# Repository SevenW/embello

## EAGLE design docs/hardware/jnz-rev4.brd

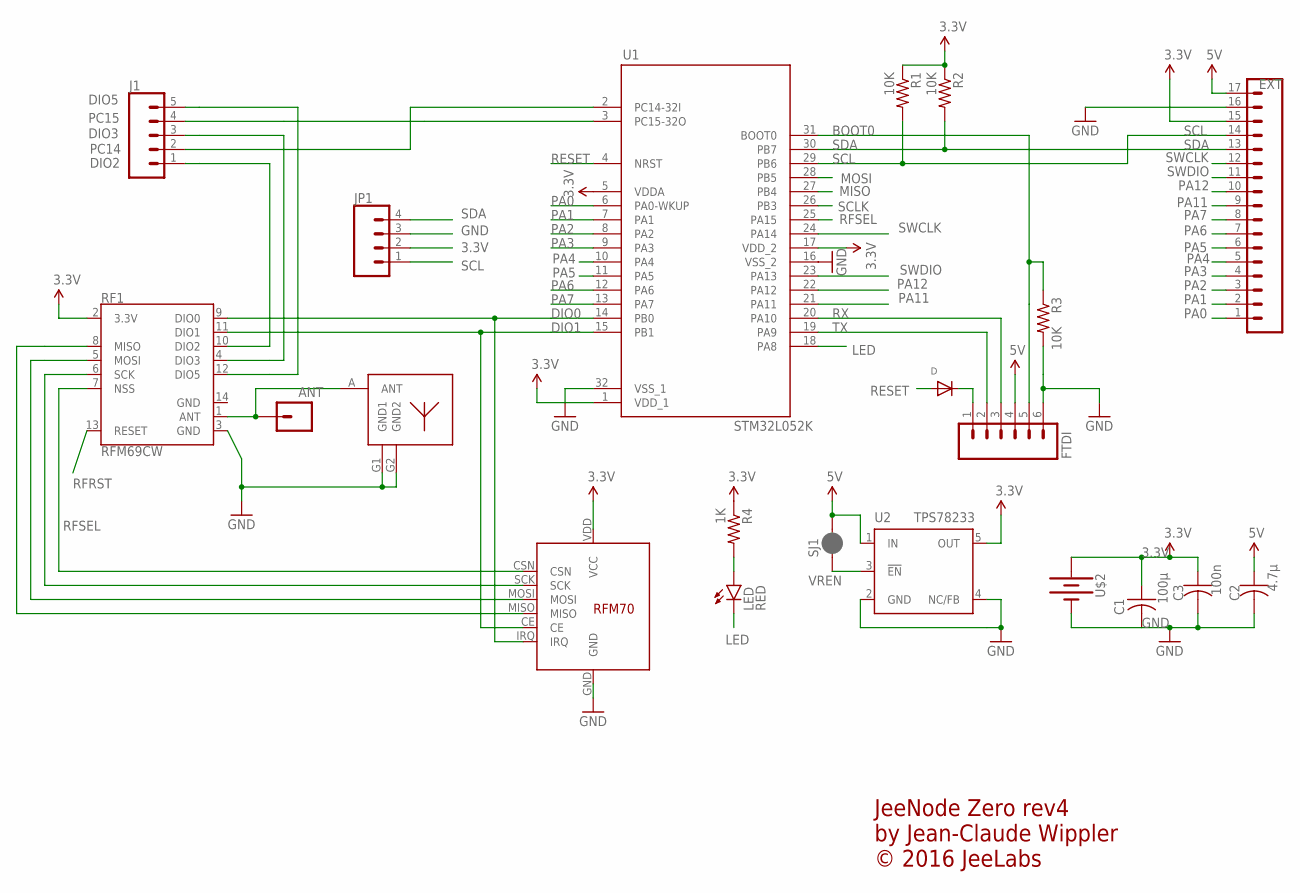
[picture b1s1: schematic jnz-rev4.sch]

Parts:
ANT: CONN_01PTH_NO_SILK_KIT; 1X01NS_KIT
C1: 100µ; C1206
C2: 4.7µ; C0805
C3: 100n; C0603
D: DIODESOD-323F; SOD-323F
EXT: CONN_17NOSILK; 1X17_NO_SILK
FTDI: CONN_06NO_SILK_FEMALE_PTH; 1X06_NO_SILK
J1: CONN_05NO_SILK; 1X05_NO_SILK
JP1: CONN_04SMD_RA_FEMALE; 1X04_SMD_RA_FEMALE
LED: RED; LED-0603
R1, R2, R3: 10K; R0603
R4: 1K; R0603
RF1: RFM69CW; RFM69CW-XXXS2
RF2: RFM75; RFM70
SJ1: JUMPER-SMT_2_NC_PASTE_NO-SILK; SMT-JUMPER_2_NC_PASTE_NO-SILK
U1: STM32L052K; TQFP32-08
U2: TPS78233; SOT23-DBV
U$1: UFL
U$2: BATTERY-20MM_SMD_4LEGS; BATTCON_20MM_4LEGS

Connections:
3.3V: C1.1, C3.1, EXT.15, JP1.2, R1.1, R2.1, R4.1, RF1.2 (3.3V), RF2.VDD (VCC), U1.1 (VDD_1), U1.5 (VDDA), U1.17 (VDD_2), U2.5 (OUT), U$2.POSITIVE@1 (+), U$2.POSITIVE@2 (+), U$2.POSITIVE@3 (+), U$2.POSITIVE@4 (+)
5V: C2.1, EXT.17, FTDI.4, SJ1.2, U2.1 (IN)
BOOT0: FTDI.5, R3.1, U1.31 (BOOT0)
DIO0: RF1.9 (DIO0), RF2.IRQ, U1.14 (PB0)
DIO1: RF1.11 (DIO1), RF2.CE, U1.15 (PB1)
DIO2: J1.1, RF1.10 (DIO2)
DIO3: J1.3, RF1.4 (DIO3)
DIO5: J1.5, RF1.12 (DIO5)
GND: C1.2, C2.2, C3.2, EXT.16, FTDI.6, JP1.3, R3.2, RF1.3 (GND), RF1.14 (GND), RF2.GND, U1.16 (VSS_2), U1.32 (VSS_1), U2.2 (GND), U2.4 (NC/FB), U$1.G1 (GND1), U$1.G2 (GND2), U$2.NEGATIVE (-)
LED: LED.C, U1.18 (PA8)
MISO: RF1.8 (MISO), RF2.MISO, U1.27 (PB4)
MOSI: RF1.5 (MOSI), RF2.MOSI, U1.28 (PB5)
unnamed: D.C, FTDI.1
unnamed: LED.A, R4.2
unnamed: ANT.1, RF1.1 (ANT), U$1.A (ANT)
PA0: EXT.1, U1.6 (PA0-WKUP)
PA1: EXT.2, U1.7 (PA1)
PA2: EXT.3, U1.8 (PA2)
PA3: EXT.4, U1.9 (PA3)
PA4: EXT.5, U1.10 (PA4)
PA5: EXT.6, U1.11 (PA5)
PA6: EXT.7, U1.12 (PA6)
PA7: EXT.8, U1.13 (PA7)
PA11: EXT.9, U1.21 (PA11)
PA12: EXT.10, U1.22 (PA12)
PC14: J1.2, U1.2 (PC14-32I)
PC15: J1.4, U1.3 (PC15-32O)
RESET: D.A, U1.4 (NRST)
RFRST: RF1.13 (RESET)
RFSEL: RF1.7 (NSS), RF2.CSN, U1.25 (PA15)
RX: FTDI.3, U1.20 (PA10)
SCL: EXT.14, JP1.1, R1.2, U1.29 (PB6)
SCLK: RF1.6 (SCK), RF2.SCK, U1.26 (PB3)
SDA: EXT.13, JP1.4, R2.2, U1.30 (PB7)
SWCLK: EXT.12, U1.24 (PA14)
SWDIO: EXT.11, U1.23 (PA13)
TX: FTDI.2, U1.19 (PA9)
VREN: SJ1.1, U2.3 (!EN)

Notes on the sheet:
JeeNode Zero rev4 by Jean-Claude Wippler © 2016 JeeLabs

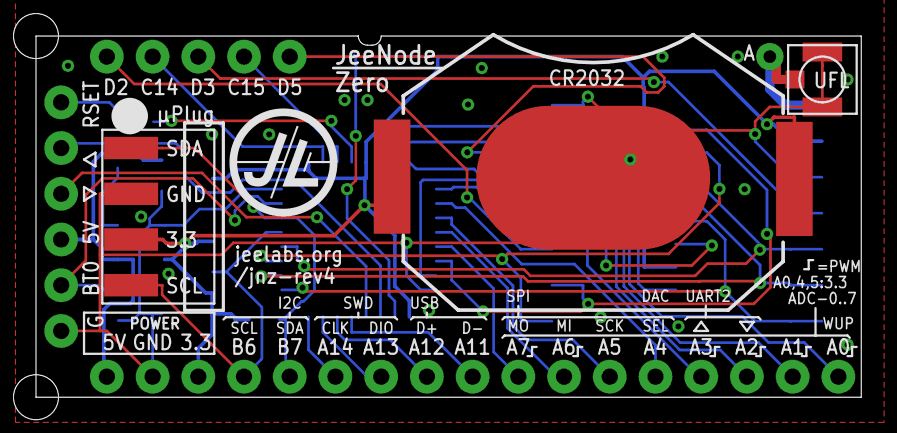
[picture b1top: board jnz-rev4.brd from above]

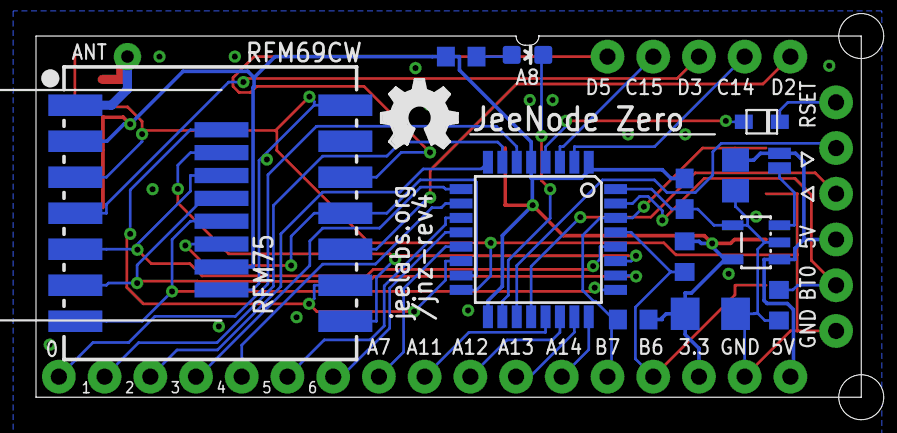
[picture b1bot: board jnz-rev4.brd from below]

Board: 2 copper layers, 45.8 x 20.1 mm, 22 parts (15 on the bottom side), 37 nets.

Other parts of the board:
LOGO1: OSHW_LOGO_FILLX0150-NT; OSHW_FILLX150_NOTEXT

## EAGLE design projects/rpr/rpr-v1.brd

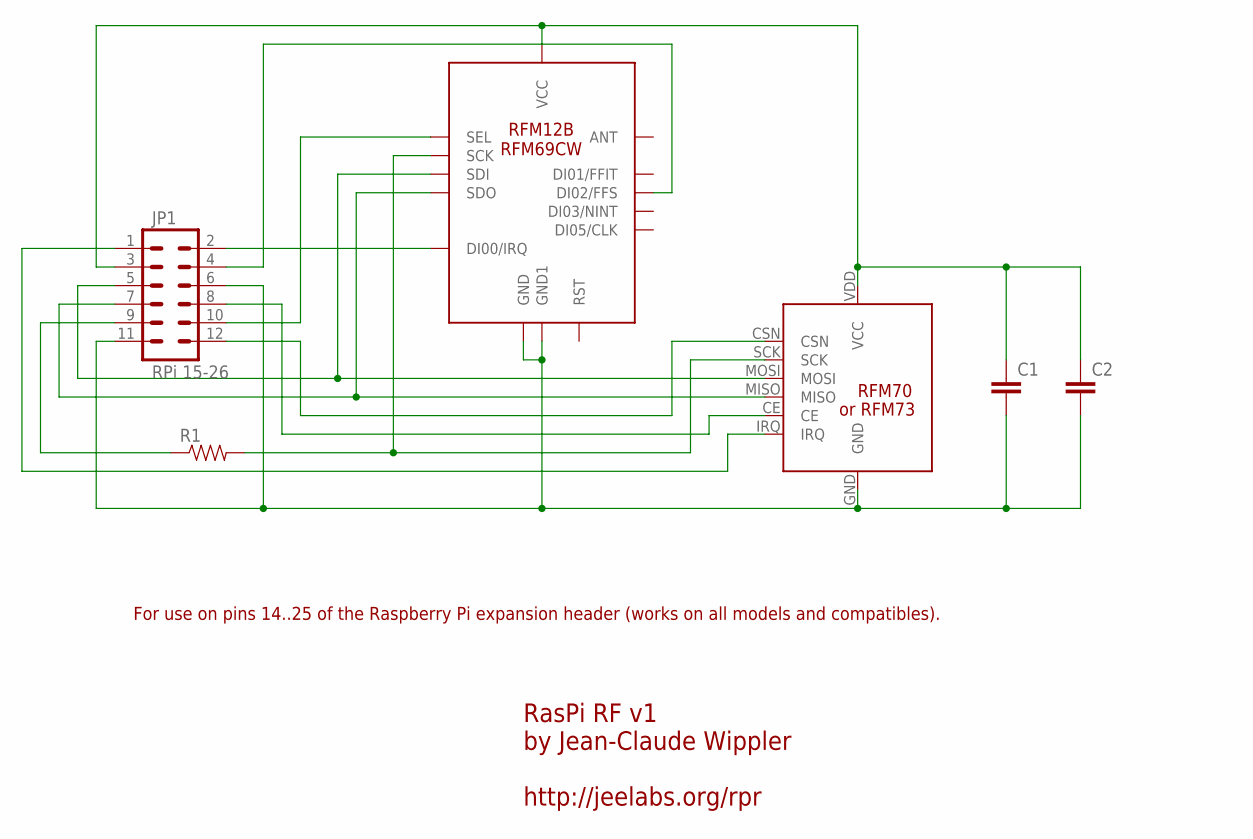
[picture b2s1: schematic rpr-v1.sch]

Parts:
C1, C2: CAP0805; 0805
JP1: RPi 15-26; 2X6
R1: RESISTOR0603-RES; 0603-RES
RFM12B/69CW: RFM12B/69CW
U$1: RFM70

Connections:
GND: C1.2, C2.2, JP1.6, JP1.11, RFM12B/69CW.GND, RFM12B/69CW.GND1, U$1.GND
unnamed: C1.1, C2.1, JP1.3, RFM12B/69CW.VDD (VCC), U$1.VDD (VCC)
unnamed: JP1.12, U$1.CSN
unnamed: JP1.10, RFM12B/69CW.SEL
unnamed: JP1.5, RFM12B/69CW.SDI, U$1.MOSI
unnamed: JP1.7, RFM12B/69CW.SDO, U$1.MISO
unnamed: JP1.9, R1.1
unnamed: R1.2, RFM12B/69CW.SCK, U$1.SCK
unnamed: JP1.8, U$1.CE
unnamed: JP1.1, U$1.IRQ
unnamed: JP1.2, RFM12B/69CW.IRQ (DI00/IRQ)
unnamed: JP1.4, RFM12B/69CW.FFS (DI02/FFS)

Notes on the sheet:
RasPi RF v1 by Jean-Claude Wippler http://jeelabs.org/rpr
For use on pins 14..25 of the Raspberry Pi expansion header (works on all models and compatibles).
or RFM73

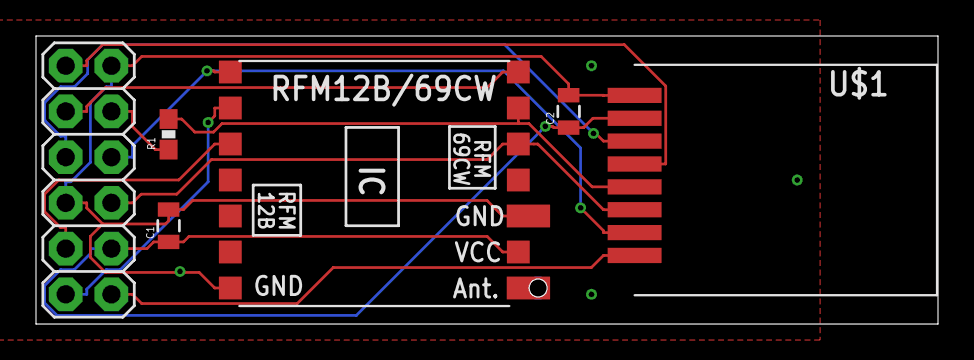
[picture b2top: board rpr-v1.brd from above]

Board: 2 copper layers, 50.1 x 16.0 mm, 6 parts (0 on the bottom side), 12 nets.

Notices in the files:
parts and their libraries:
SparkFun-LED: Licensing: Creative Commons ShareAlike 4.0 International - https://creativecommons.org/licenses/by-sa/4.0
